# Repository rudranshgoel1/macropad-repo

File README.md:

# Macropad

It is an 8 key macropad, which helps users control small tasks which are repetitive easily. like closing or opening new tabs, or  even opening a certain website with a click of a button. there are a few silkscreen images to enhance the visuals of this macropad.

## What's in here

- `macropad-pcb.kicad_pro` - KiCad project file
- `macropad-pcb.kicad_sch` - schematic
- `macropad-pcb.kicad_pcb` - board layout
- `image1.png`, `image2.png`, `image3.png` - board renders
- `image4.png` - pcb routing

## Preview

## Credits

Made by Rudransh Goel (stolen_username on slack)

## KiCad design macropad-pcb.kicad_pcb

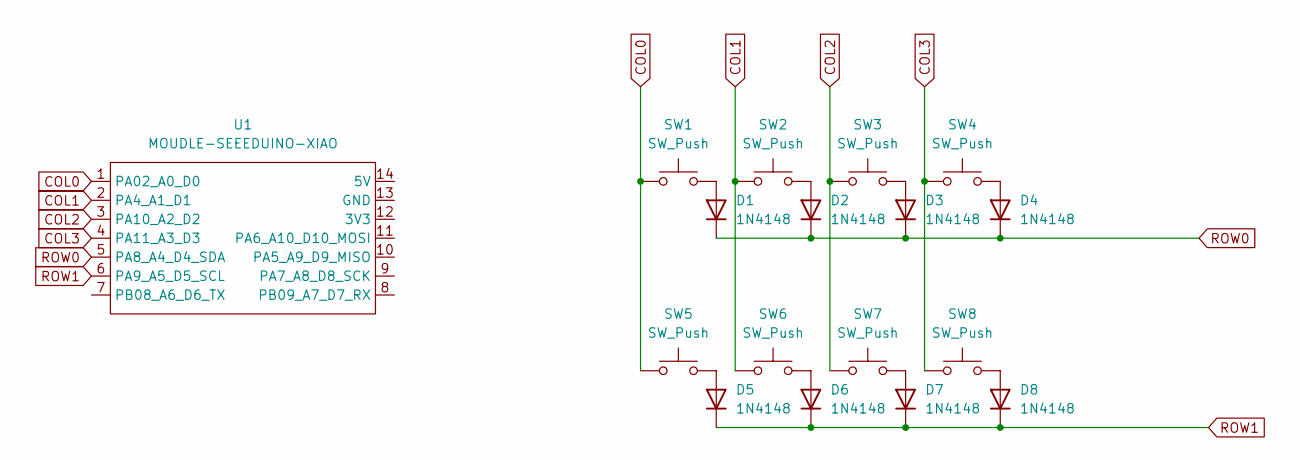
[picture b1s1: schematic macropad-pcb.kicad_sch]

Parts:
D1, D2, D3, D4, D5, D6, D7, D8: 1N4148; D_DO-35_SOD27_P7.62mm_Horizontal
SW1, SW2, SW3, SW4, SW5, SW6, SW7, SW8: SW_Push; SW_Cherry_MX_1.00u_PCB
U1: MOUDLE-SEEEDUINO-XIAO; XIAO-RP2040-DIP

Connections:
COL0: SW1.1, SW5.1, U1.1 (PA02_A0_D0)
COL1: SW2.1, SW6.1, U1.2 (PA4_A1_D1)
COL2: SW3.1, SW7.1, U1.3 (PA10_A2_D2)
COL3: SW4.1, SW8.1, U1.4 (PA11_A3_D3)
unnamed: D1.2 (A), SW1.2
unnamed: D2.2 (A), SW2.2
unnamed: D3.2 (A), SW3.2
unnamed: D4.2 (A), SW4.2
unnamed: D5.2 (A), SW5.2
unnamed: D6.2 (A), SW6.2
unnamed: D7.2 (A), SW7.2
unnamed: D8.2 (A), SW8.2
ROW0: D1.1 (K), D2.1 (K), D3.1 (K), D4.1 (K), U1.5 (PA8_A4_D4_SDA)
ROW1: D5.1 (K), D6.1 (K), D7.1 (K), D8.1 (K), U1.6 (PA9_A5_D5_SCL)

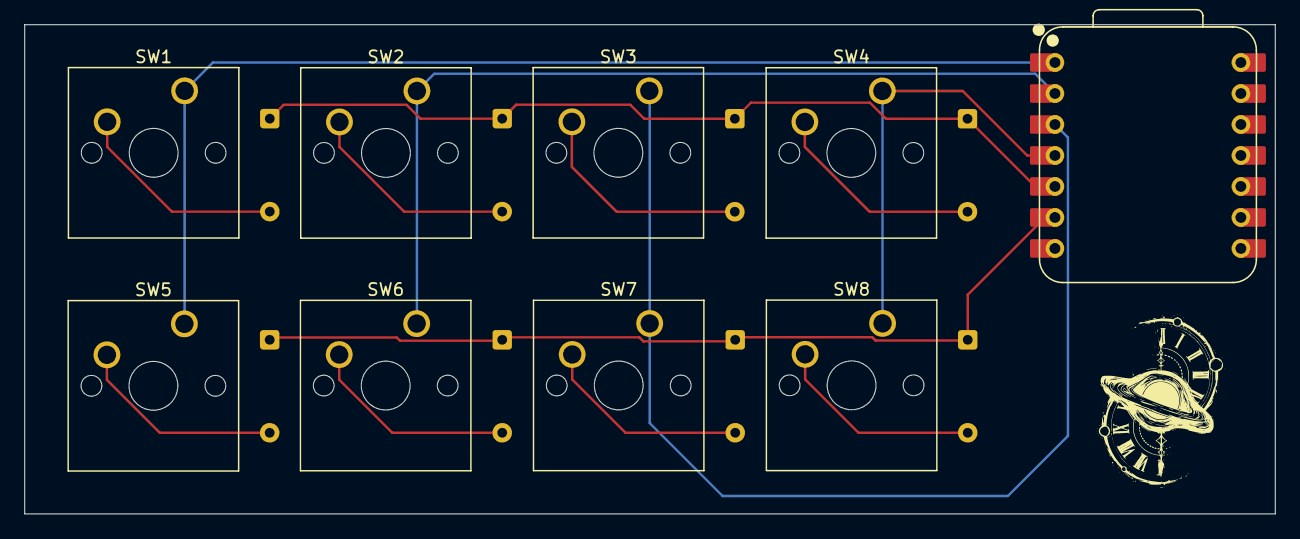
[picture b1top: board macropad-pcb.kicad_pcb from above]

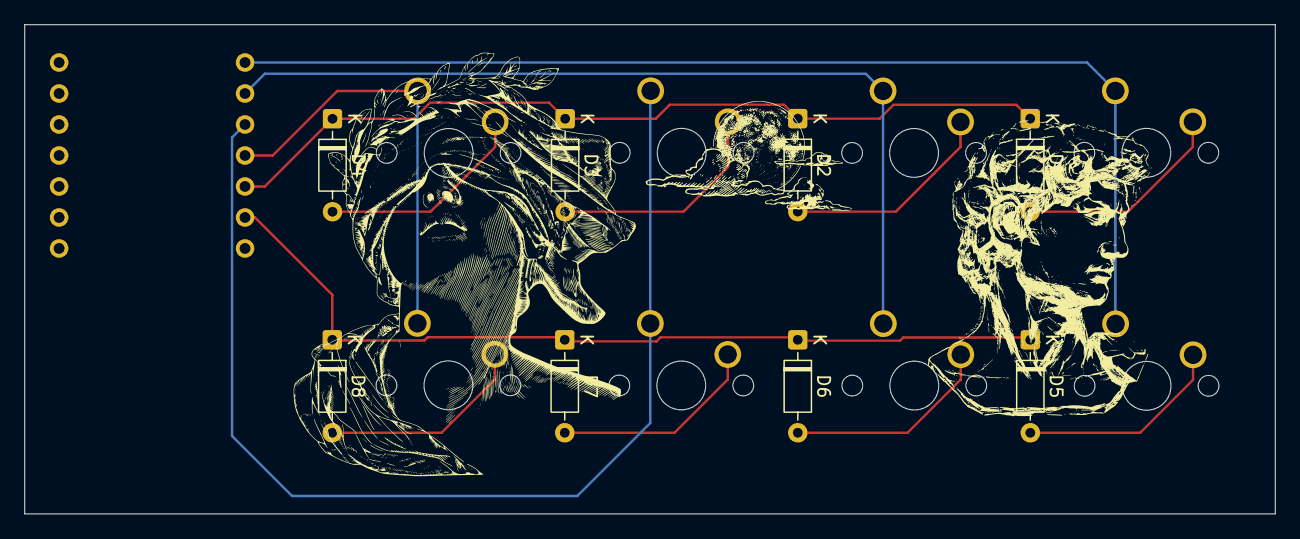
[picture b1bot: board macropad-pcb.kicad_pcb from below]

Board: 2 copper layers, 102.5 x 40.1 mm, 17 parts (8 on the bottom side), 14 nets.

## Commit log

2026-04-18 main commit
2026-04-18 readme
2026-04-18 pcb routing
2026-04-18 pcb image
